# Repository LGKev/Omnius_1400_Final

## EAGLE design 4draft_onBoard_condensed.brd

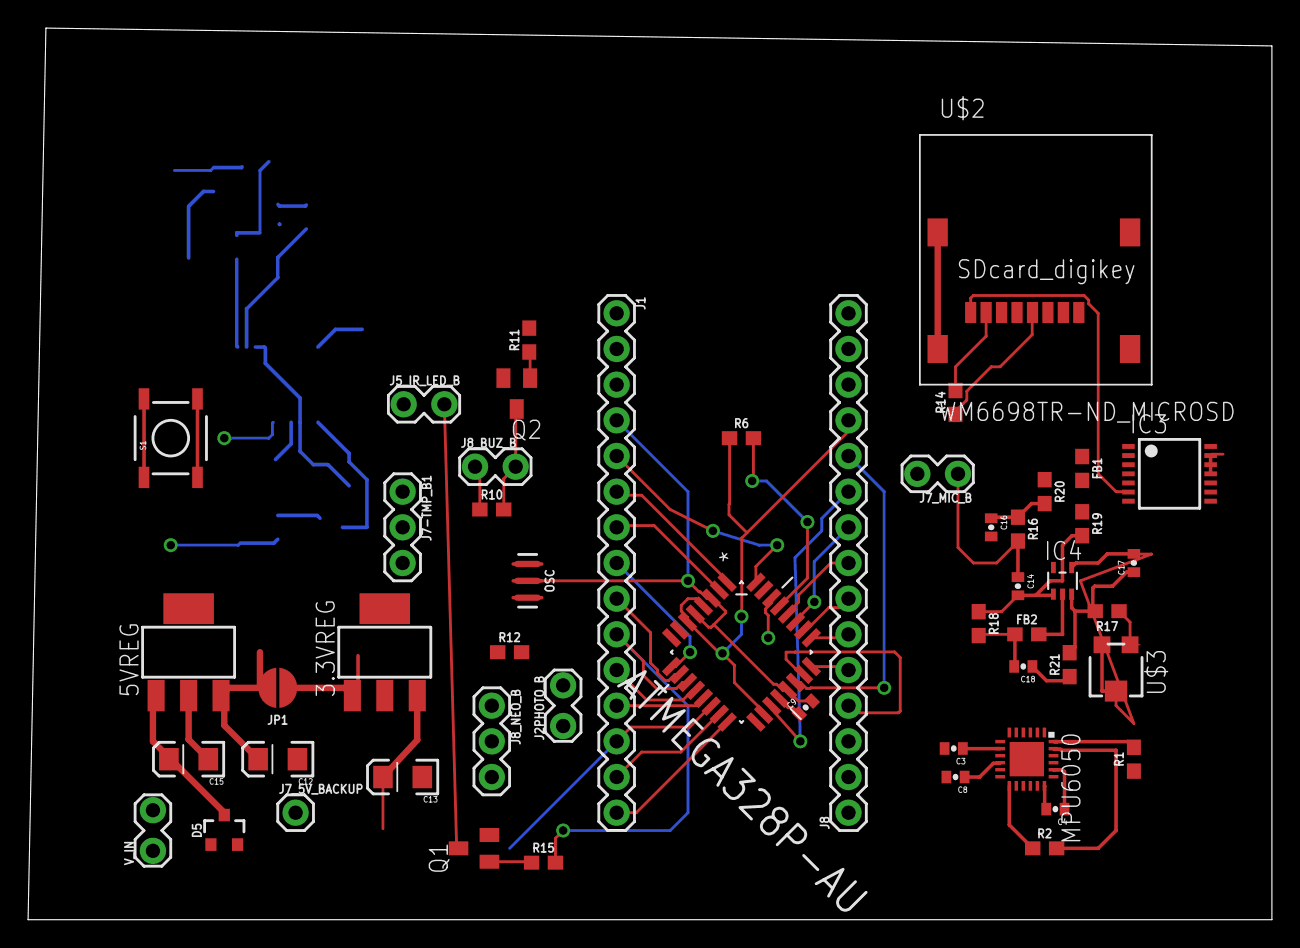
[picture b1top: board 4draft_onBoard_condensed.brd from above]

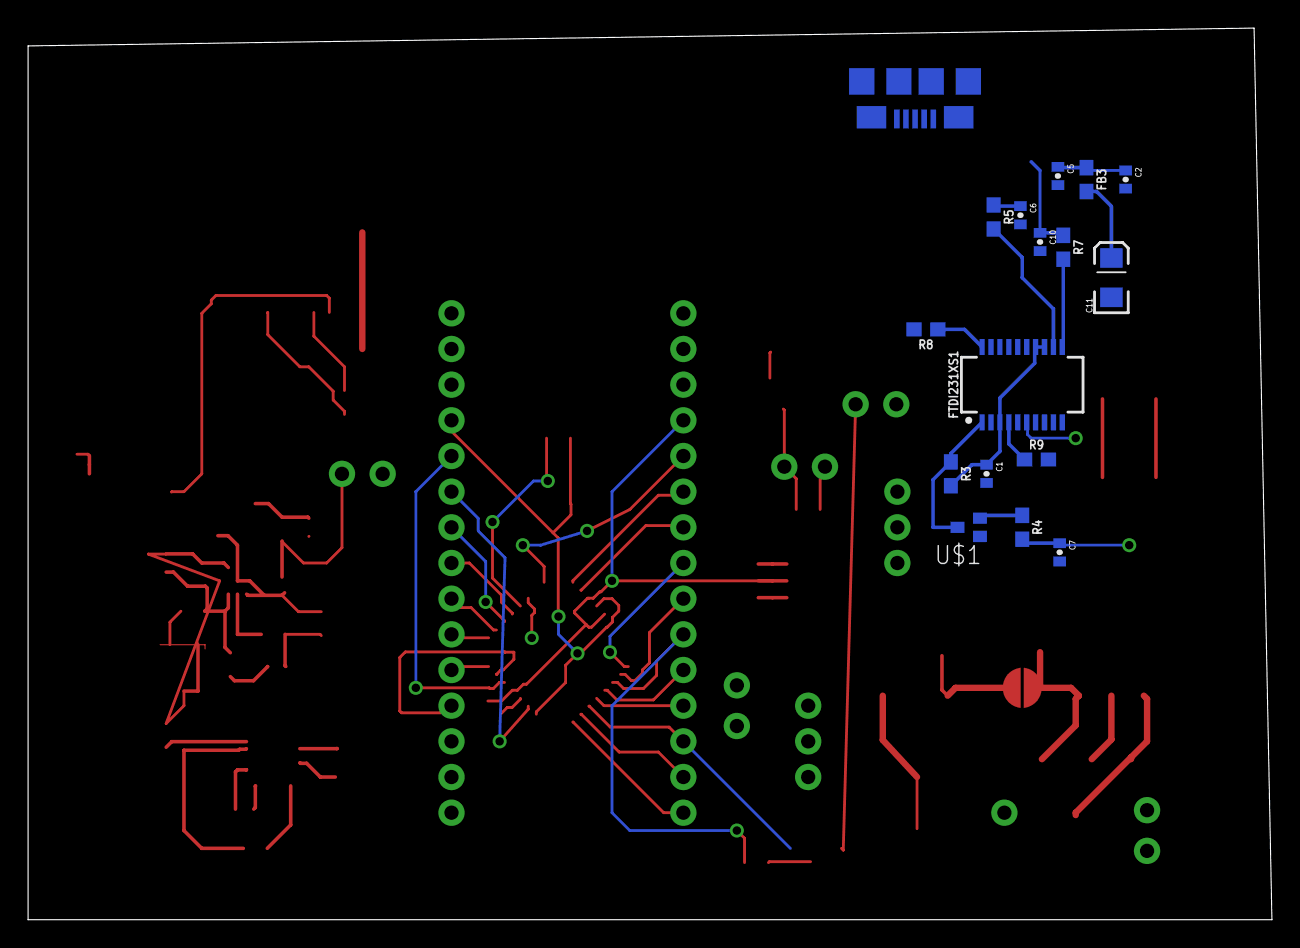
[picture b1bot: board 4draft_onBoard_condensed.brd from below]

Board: 2 copper layers, 88.6 x 63.5 mm, 68 parts (17 on the bottom side), 59 nets.

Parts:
3.3VREG, 5VREG: SOT223
ATMEGA328P-AU: ATMEGA328P-AU; QFP80P900X900X120-32N
C1, C2, C5, C7, C8, C16: .1uF; 0402-CAP
C3: 10nF; 0402-CAP
C4: 2.2nF; 0402-CAP
C6, C10: 47pF; 0402-CAP
C9: .01 uF; 0402-CAP
C11, C12, C13: 10uF; EIA3216
C14: .01uF; 0402-CAP
C15: 47uF; EIA3216
C17: 100pF; 0402-CAP
C18: 10uF; 0402-CAP
D5: 700mA/40V/533mV; SOT23-3
FB1, FB2, FB3: 30Ω/1.8A; 0603
FTDI231XS1: FT231XS; SSOP20_L
IC3: 74ABT125PW; TSSOP14
IC4: MAX4466KS; SC70-5
J1, J8: 1X15
J2: USB_MINI-B_DIGIKEY; MICRO-USB-DIGIKEY-FCI2
J2PHOTO_B, J5_IR_LED_B, J7_MIC_B, J8_BUZ_B: 1X02_LOCK
J7-TMP_B1, J8_NEO_B: 1X03
J7_5V_BACKUP: 1X01
JP1: JUMPER-SMT_2_NO_NO-SILK_ROUND; SMT-JUMPER_2_NO_NO-SILK_ROUND
MPU6050: MPU-6050; QFN24-4X4
OSC: RESONATOR-SMD-3.2X1.3
Q1: NPN 40V 1A SOT-23; SOT23
Q2: SOT23
R1, R2, R3, R4, R6, R14: 10k; 0603
R5, R7: 27; 0603
R8, R9, R10, R11, R15, R16, R20, R21: 1k; 0603
R12: 2.2K; 0603
R17: 22k; 0603
R18, R19: 1M; 0603
S1: TAC_SWITCHSMD; TACTILE-SWITCH-SMD
U$1: 1N7002PW; SOT323W_INFINEON
U$2: WM6698TR-ND_MICROSD; MICROSD2
U$3: TC33X-2POT; TC33X-2
V_IN: 1X02_LOCK

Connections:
2.2NF: C4.1, MPU6050.20
3.3V: 3.3VREG.3, C13.A, IC3.11, IC3.12, IC3.13, R14.1, U$2.VDD
3.3VFTDI: C1.1, FTDI231XS1.3, FTDI231XS1.13, FTDI231XS1.14, R3.2, U$1.1
5REGOUT: 5VREG.3, C12.A, J7_5V_BACKUP.1, JP1.2
5V: 3.3VREG.1, ATMEGA328P-AU.4, ATMEGA328P-AU.6, ATMEGA328P-AU.18, C2.1, C5.1, C11.A, FB1.1, FB3.1, FB3.2, FTDI231XS1.15, J2.VCC, J5_IR_LED_B.1, J7-TMP_B1.1, J8.12, J8_NEO_B.2, JP1.1, MPU6050.13, R1.1, R2.1, R4.1, R6.1, R12.1, U$1.3
10NF: C3.1, MPU6050.8
.UF: C8.1, MPU6050.10
A0: ATMEGA328P-AU.23, J2PHOTO_B.2, J8.4, R12.2
A1: ATMEGA328P-AU.24, J7-TMP_B1.2, J8.5
A2: ATMEGA328P-AU.25, J8.6
A3: ATMEGA328P-AU.26, J8.7
A6: ATMEGA328P-AU.19, C17.2, IC4.4, J8.10, U$3.2, U$3.3
A7: ATMEGA328P-AU.22, J8.11
AVCC: FB1.2, IC3.14, IC4.5, R19.1, R20.1
BUZ+: J8_BUZ_B.1, R10.1
BUZ-: J8_BUZ_B.2, Q2.3, R10.2
D2: ATMEGA328P-AU.32, J1.5
D3: ATMEGA328P-AU.1, J1.6, R11.2
D4: ATMEGA328P-AU.2, J1.7
D5: ATMEGA328P-AU.9, J1.8
D6: ATMEGA328P-AU.10, J1.9
D7: ATMEGA328P-AU.11, J1.10, R15.2
D8: ATMEGA328P-AU.12, J1.11
D9: ATMEGA328P-AU.13, J1.12, J8_NEO_B.1
D+: C6.1, J2.D+, R5.1
D-: C10.1, J2.D-, R7.1
DTR: C7.1, R4.2, S1.1, S1.2
DTR_FTDI: FTDI231XS1.1, R3.1, U$1.2
GND: 3.3VREG.2, 3.3VREG.4, 5VREG.2, 5VREG.4, ATMEGA328P-AU.3, ATMEGA328P-AU.5, ATMEGA328P-AU.21, C1.2, C2.2, C3.2, C4.2, C5.2, C6.2, C8.2, C9.2, C10.2, C11.C, C12.C, C13.C, C15.C, C16.2, C18.2, FB2.1, FB2.2, FTDI231XS1.6, FTDI231XS1.16, IC3.1, IC3.4, IC3.7, IC3.10, IC4.2, J1.4, J2.GND, J2PHOTO_B.1, J7-TMP_B1.3, J7_MIC_B.2, J8_NEO_B.3, MPU6050.18, OSC.2, Q1.2, Q2.2, R18.2, S1.3, S1.4, U$2.GND, U$2.GND2, U$2.GND3, U$2.GND4, U$2.VSS, V_IN.2
IR_-: J5_IR_LED_B.2, Q1.3
IR_LED: Q1.1, R15.1
MISO: ATMEGA328P-AU.16, J1.15, R14.2, U$2.DAT0
MOSI: ATMEGA328P-AU.15, IC3.5, J1.14
unnamed: ATMEGA328P-AU.7, OSC.1
unnamed: ATMEGA328P-AU.8, OSC.3
unnamed: ATMEGA328P-AU.20, C9.1
unnamed: IC3.6, U$2.DAT1
unnamed: R17.1, U$3.1
unnamed: FTDI231XS1.11, R7.2
unnamed: FTDI231XS1.12, R5.2
unnamed: C16.1, R16.1, R20.2
unnamed: Q2.1, R11.1
unnamed: D5.1, V_IN.1
unnamed: C14.1, J7_MIC_B.1, R16.2
unnamed: C14.2, IC4.1, R18.1, R19.2
unnamed: C18.1, R21.1
unnamed: C17.1, IC4.3, R17.2, R21.2
RESET: ATMEGA328P-AU.29, R6.2
RX: FTDI231XS1.4, R9.1
RX-I: ATMEGA328P-AU.30, R8.2
SCK: ATMEGA328P-AU.17, IC3.2, J8.1
SCK_BUFF: IC3.3, U$2.CLK
SCL: ATMEGA328P-AU.27, J8.9, MPU6050.23, R2.2
SDA: ATMEGA328P-AU.28, C7.2, J8.8, MPU6050.24, R1.2
SS: ATMEGA328P-AU.14, IC3.9, J1.13
SS_BUFF: IC3.8, U$2.CMD
TX: FTDI231XS1.20, R8.1
TX-O: ATMEGA328P-AU.31, R9.2
VIN: 5VREG.1, C15.A, D5.3

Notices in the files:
parts and their libraries:
SparkFun-Retired: Licensing: Creative Commons ShareAlike 4.0 International - https://creativecommons.org/licenses/by-sa/4.0
